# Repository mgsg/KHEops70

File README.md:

# KHEops70 
Keyboard | Hall Effect | OrthoLinear | Programmable | Standard-sized

| WARNING: DIY project. Use at your own risk!

| Forked from the [Moonboard Keyboard](https://github.com/certainly1182/MoonBoard).

<p>&nbsp;&nbsp;&nbsp;&nbsp;&nbsp;&nbsp;&nbsp;&nbsp;</p>

## Features

- 70 HE switches, 60% case, 13x5 + 5 keys + 1 encoder + 2 potentiometers in ortholinear arrangement.
- All keys are 1u. Keycaps in uniform profile preferred (XDA, DSA...).
- QMK Firmware compatibility.
- QMK MIDI Support (Audio support buggy).
- Compatibility with "standard" widely available 60% keyboard cases.
- OLED display.

## Hardware

Design for PCBs can be found in the hardware folder.

<p>&nbsp;&nbsp;&nbsp;&nbsp;&nbsp;&nbsp;&nbsp;&nbsp;</p>

<p>&nbsp;&nbsp;&nbsp;&nbsp;&nbsp;&nbsp;&nbsp;&nbsp;</p>

## Firmware

Compiled firmware provided as is. Largely based on the [Moonboard firmware found here](https://github.com/RephlexZero/qmk_firmware/tree/adc_testing/keyboards/rephlex/moonboard). Modified keyboard.json provided.

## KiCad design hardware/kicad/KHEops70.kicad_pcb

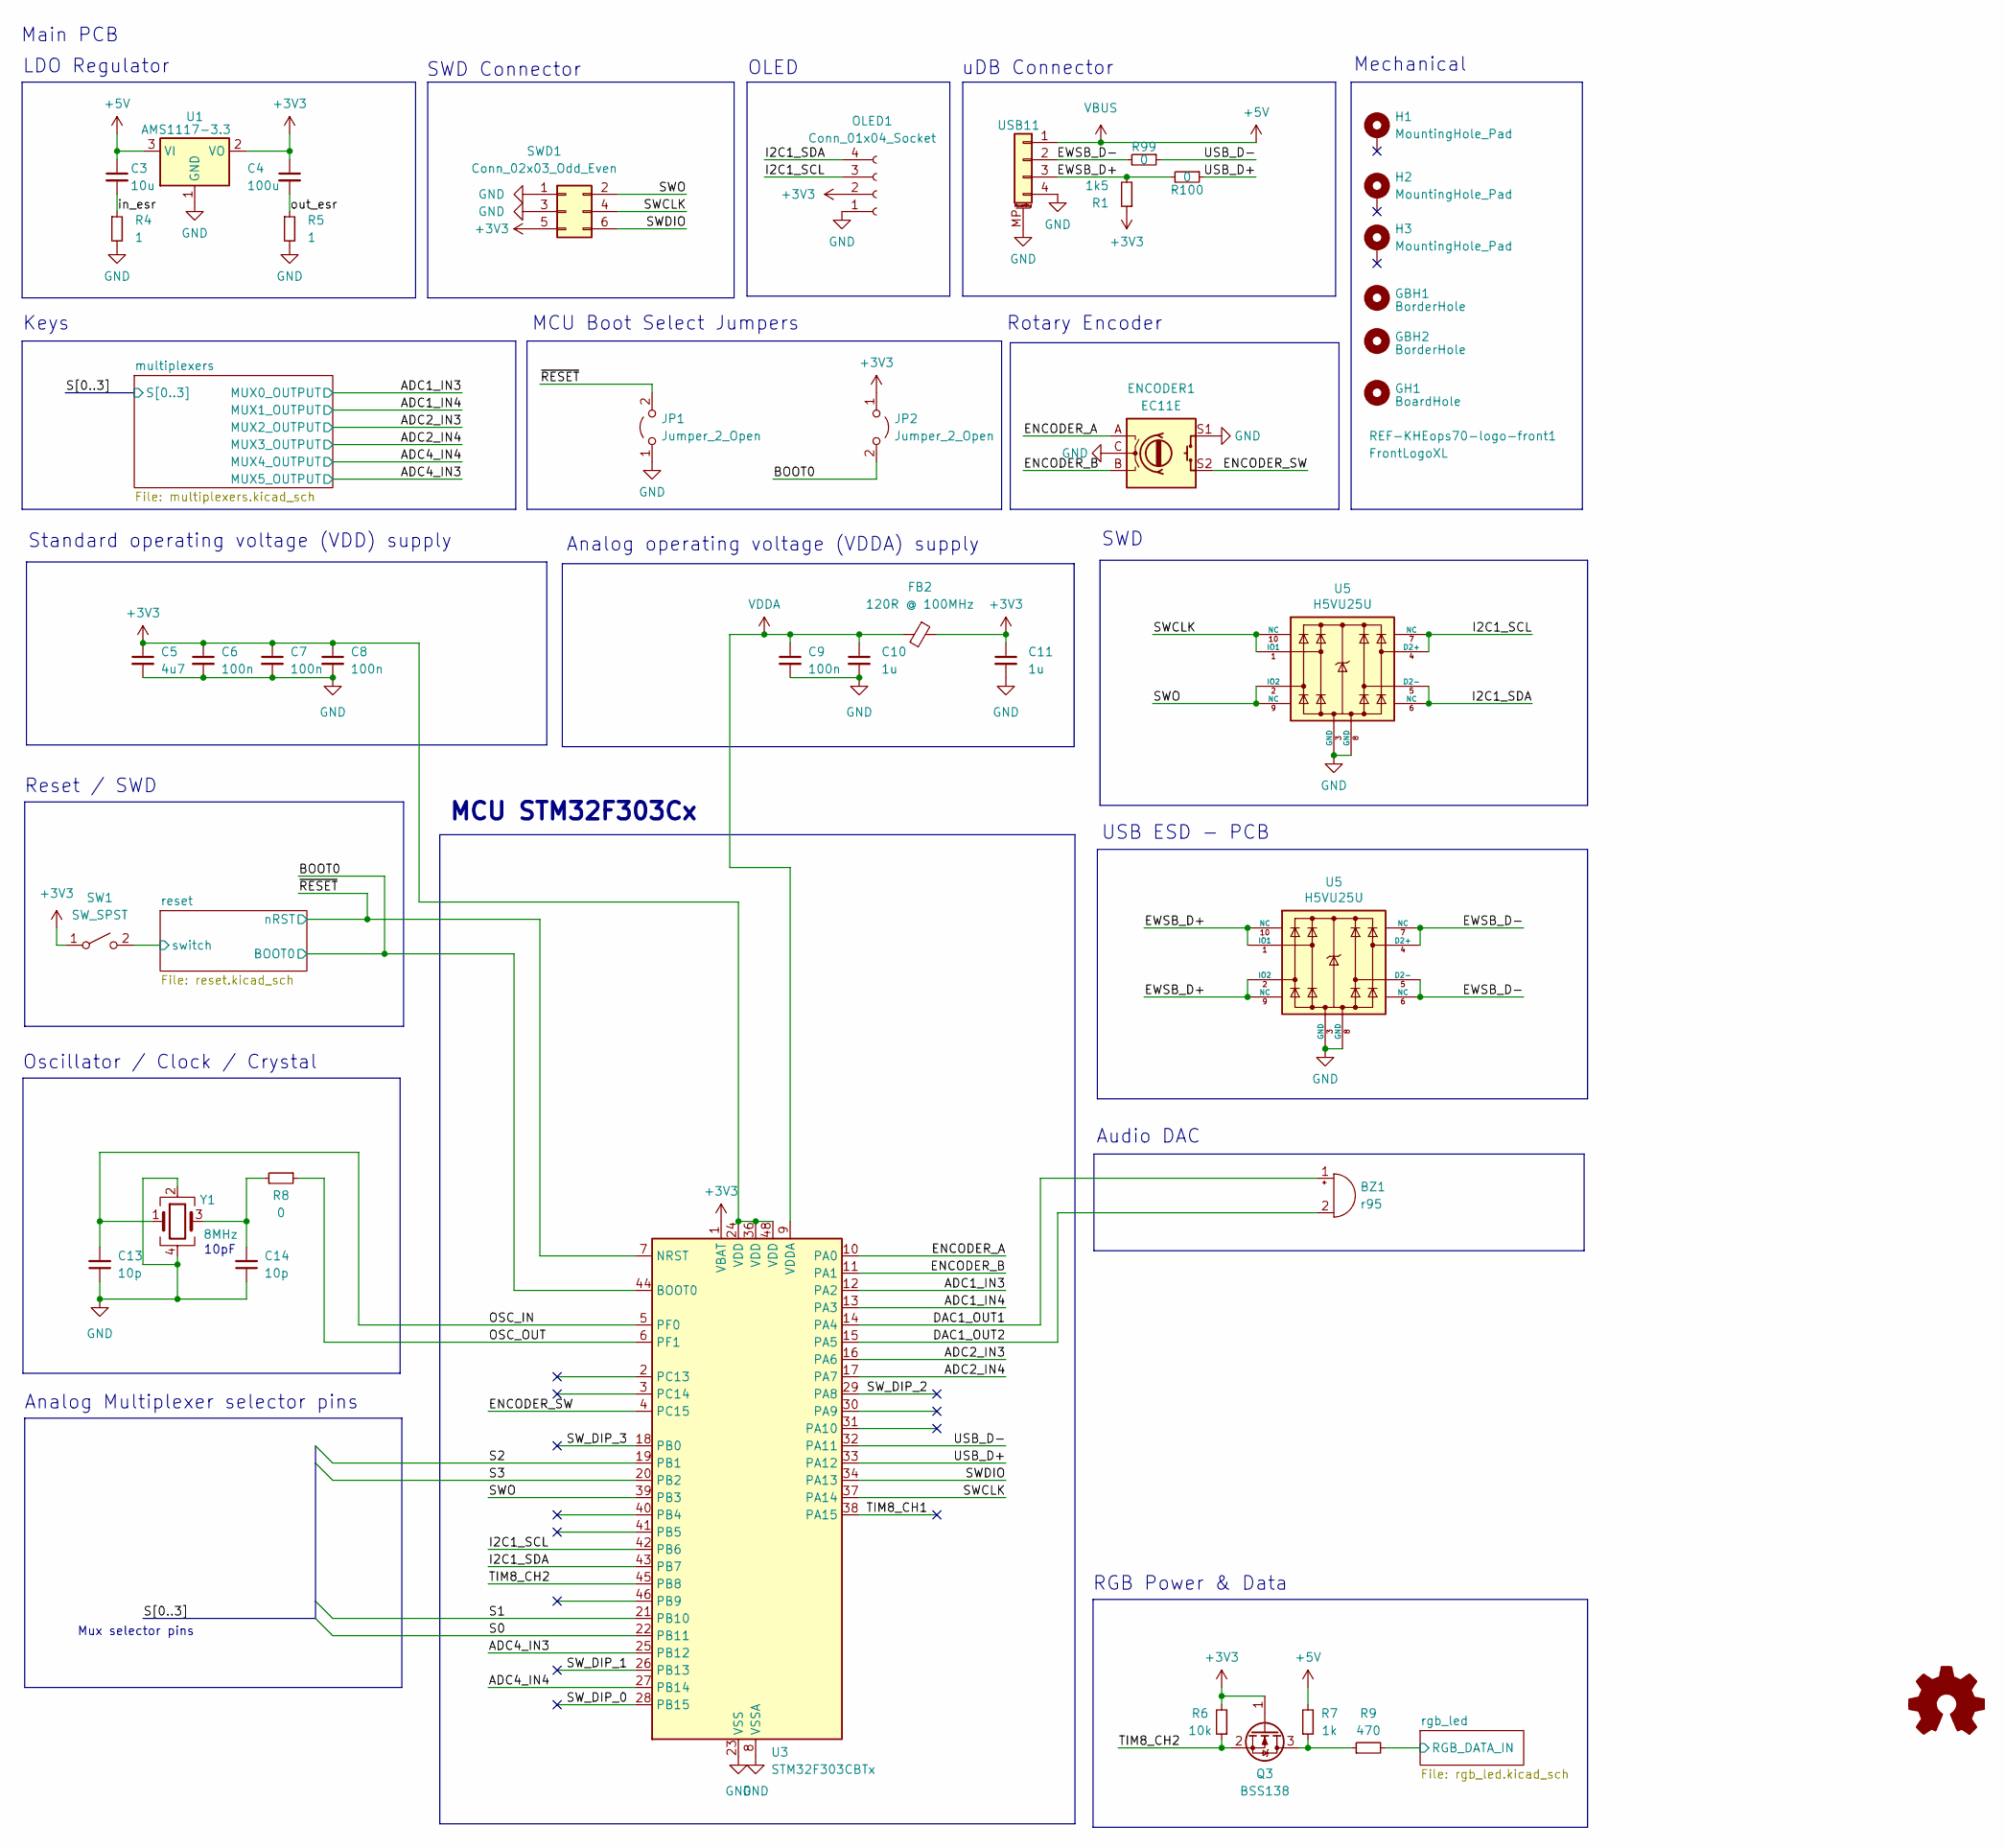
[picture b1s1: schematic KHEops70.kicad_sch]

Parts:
BZ1: r95; Buzzer_Murata_PKLCS1212E; LCSC PN C113159
C3: 10u; C_1206_3216Metric; LCSC C13585
C4: 100u; C_1206_3216Metric; LCSC C15008
C5: 4u7; C_0402_1005Metric; LCSC C23733
C6, C7, C8, C9: 100n; C_0402_1005Metric; LCSC C1525
C10, C11: 1u; C_0402_1005Metric; LCSC C52923
C13, C14: 10p; C_0402_1005Metric; LCSC C32949
ENCODER1: EC11E; ROT_Alps_EC11E-Switch
FB2: 120R @ 100MHz; L_0805_2012Metric; LCSC C79382
GBH1, GBH2: BorderHole; KHEops70-border-hole
GH1: BoardHole; KHEops70-hole
H1, H2, H3: MountingHole_Pad; 2.2mm hole
JP1, JP2: Jumper_2_Open; PinHeader_1x02_P2.54mm_Vertical
LOGO2: (no value)
OLED1: Conn_01x04_Socket; OLED Module
Q3: BSS138; SOT-23; LCSC C5224263
R1: 1k5; R_0805_2012Metric; LCSC C25867
R4, R5: 1; R_1206_3216Metric; LCSC C17928
R6: 10k; R_0805_2012Metric; LCSC C17414
R7: 1k; R_0805_2012Metric; LCSC C17513
R8, R99, R100: 0; R_0603_1608Metric_Pad0.98x0.95mm_HandSolder; LCSC C21189
R9: 470; R_0805_2012Metric; LCSC C25117
REF-KHEops70-logo-front1: FrontLogoXL; KHEops70-logo-xl
SW1: SW_SPST; SW_SPST_TL3342; LCSC C2886897
SWD1: Conn_02x03_Odd_Even; PinHeader_2x03_P2.54mm_Vertical
U1: AMS1117-3.3; SOT-223-3_TabPin2; LCSC C6186
U3: STM32F303CBTx; LQFP-48_7x7mm_P0.5mm; LCSC C108516
U5: H5VU25U; DFN2510; Manufacturer Part Number TPD4E05U06DQAR; LCSC C20615800
USB11: SM04B-SRSS-TB; JST_SH_SM04B-SRSS-TB_1x04-1MP_P1.00mm_Horizontal; Manufacturer Part Number SM04B-SRSS-TB; LCSC C160404
Y1: 8MHz; Crystal_SMD_3225-4Pin_3.2x2.5mm; LCSC C518154

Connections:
+3V3: C4.1, C5.1, C6.1, C7.1, C8.1, C11.1, FB2.1, JP2.1 (A), OLED1.2, Q3.1 (G), R1.1, R6.2, SW1.1 (A), SWD1.5, U1.2 (VO), U3.1 (VBAT), U3.24 (VDD), U3.36 (VDD), U3.48 (VDD); also elsewhere on the board
+5V: C3.1, R7.2, U1.3 (VI), USB11.1; also elsewhere on the board
/ADC1_IN3: U3.12 (PA2); also elsewhere on the board
/ADC2_IN3: U3.16 (PA6); also elsewhere on the board
/ADC2_IN4: U3.17 (PA7); also elsewhere on the board
/ADC4_IN3: U3.25 (PB12); also elsewhere on the board
/ADC4_IN4: U3.27 (PB14); also elsewhere on the board
/BOOT0: JP2.2 (B), U3.44 (BOOT0); also elsewhere on the board
/DAC1_OUT1: BZ1.1 (-), U3.14 (PA4)
/DAC1_OUT2: BZ1.2 (+), U3.15 (PA5)
/ENCODER_A: ENCODER1.A, U3.10 (PA0)
/ENCODER_B: ENCODER1.B, U3.11 (PA1)
/ENCODER_SW: ENCODER1.S2, U3.4 (PC15)
/OSC_IN: C13.2, U3.5 (PF0), Y1.1
/OSC_OUT: R8.1, U3.6 (PF1)
/S1: U3.21 (PB10); also elsewhere on the board
/S2: U3.19 (PB1); also elsewhere on the board
/S3: U3.20 (PB2); also elsewhere on the board
/SWDIO: SWD1.6, U3.34 (PA13)
/SW_DIP_0: U3.28 (PB15)
/SW_DIP_1: U3.26 (PB13)
/SW_DIP_2: U3.29 (PA8)
/SW_DIP_3: U3.18 (PB0)
/TIM8_CH1: U3.38 (PA15)
/TIM8_CH2: Q3.2 (S), R6.1, U3.45 (PB8)
/USB_D+: R100.1, U3.33 (PA12)
/USB_D-: R99.1, U3.32 (PA11)
/in_esr: C3.2, R4.1
/out_esr: C4.2, R5.1
/reset/switch: SW1.2 (B); also elsewhere on the board
/rgb_led/RGB_DATA_IN: R9.2; also elsewhere on the board
/~RESET: JP1.2 (B), U3.7 (NRST); also elsewhere on the board
unnamed: C14.2, R8.2, Y1.3
unnamed: Q3.3 (D), R7.1, R9.1
VDDA: C9.1, C10.1, FB2.2, U3.9 (VDDA)

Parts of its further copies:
U10, U11: H5VU25U; DFN2510; Manufacturer Part Number TPD4E05U06DQAR; LCSC C20615800

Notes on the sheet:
Standard operating voltage (VDD) supply
Mechanical
Keys
Analog Multiplexer selector pins
Mux selector pins
SWD Connector
SWD
OLED
Audio DAC
10pF
MCU Boot Select Jumpers
USB ESD - PCB
RGB Power & Data
Reset / SWD
Rotary Encoder
Analog operating voltage (VDDA) supply
uDB Connector
MCU STM32F303Cx
LDO Regulator
Main PCB
Oscillator / Clock / Crystal

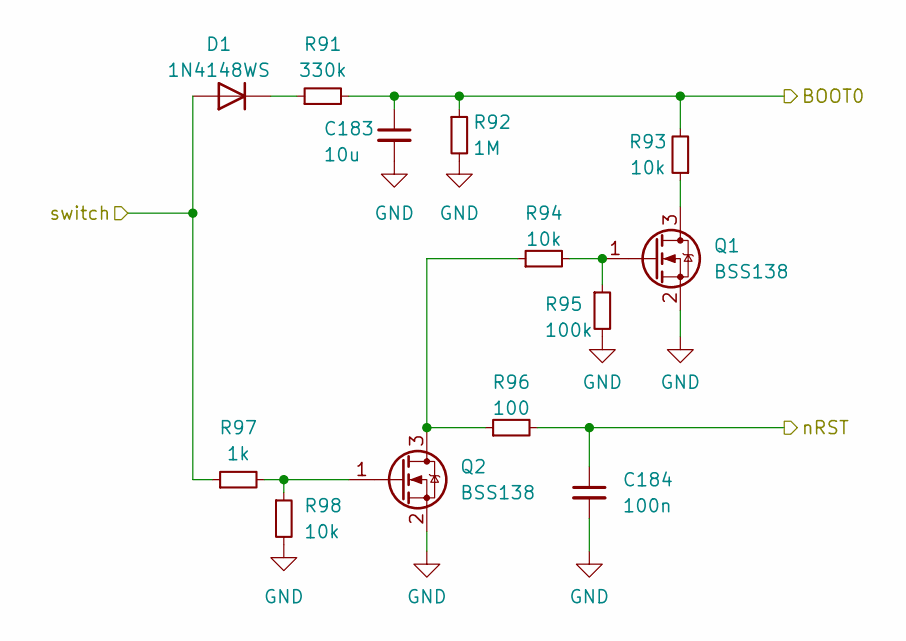
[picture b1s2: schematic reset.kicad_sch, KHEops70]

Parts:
C183: 10u; C_1206_3216Metric; LCSC C13585
C184: 100n; C_0805_2012Metric; LCSC C49678
D1: 1N4148WS; D_SOD-323; LCSC C2128
Q1, Q2: BSS138; SOT-23; LCSC C5224263
R91: 330k; R_0603_1608Metric; LCSC C23137
R92: 1M; R_0603_1608Metric; LCSC C22935
R93, R98: 10k; R_0603_1608Metric; LCSC C17414
R94: 10k; R_0805_2012Metric; LCSC C17414
R95: 100k; R_0805_2012Metric; LCSC C25741
R96: 100; R_0805_2012Metric; LCSC C25076
R97: 1k; R_0603_1608Metric; LCSC C21190

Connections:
/BOOT0: C183.1, R91.2, R92.1, R93.2; also elsewhere on the board
/reset/switch: D1.2 (A), R97.1; also elsewhere on the board
/~RESET: C184.1, R96.2; also elsewhere on the board
unnamed: D1.1 (K), R91.1
unnamed: Q1.3 (D), R93.1
unnamed: Q1.1 (G), R94.2, R95.1
unnamed: Q2.3 (D), R94.1, R96.1
unnamed: Q2.1 (G), R97.2, R98.1

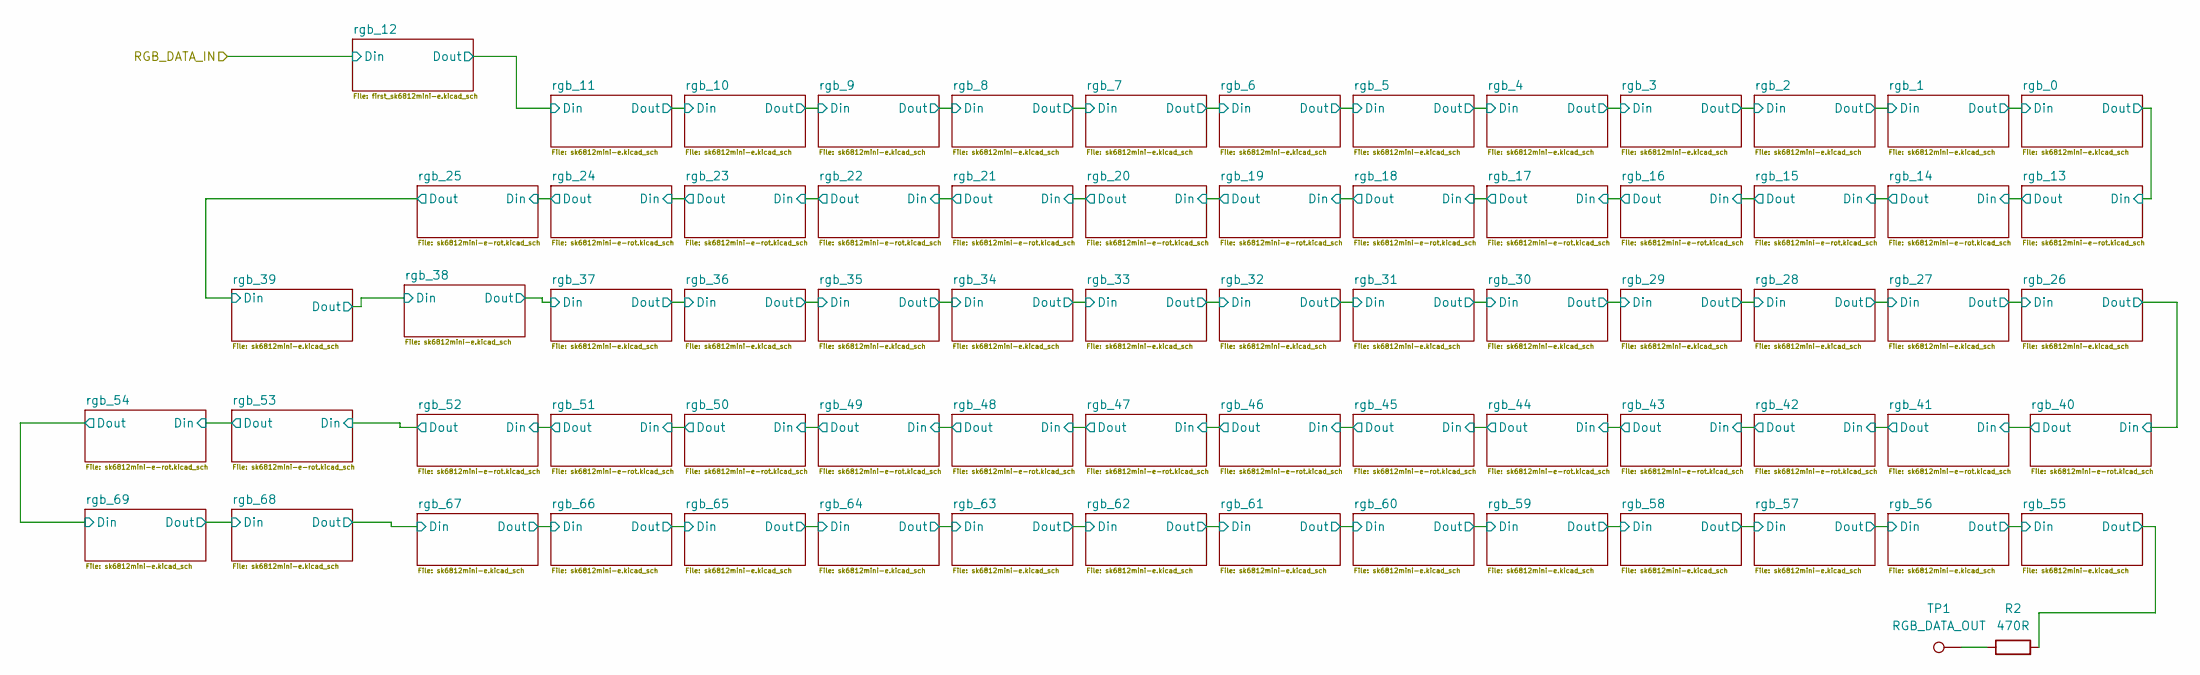
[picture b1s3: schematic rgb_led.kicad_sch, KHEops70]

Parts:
R2: 470R; R_0805_2012Metric; LCSC C25117
TP1: RGB_DATA_OUT; TestPoint_Pad_D1.5mm

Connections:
/rgb_led/rgb_55/Dout: R2.2; also elsewhere on the board
unnamed: R2.1, TP1.1

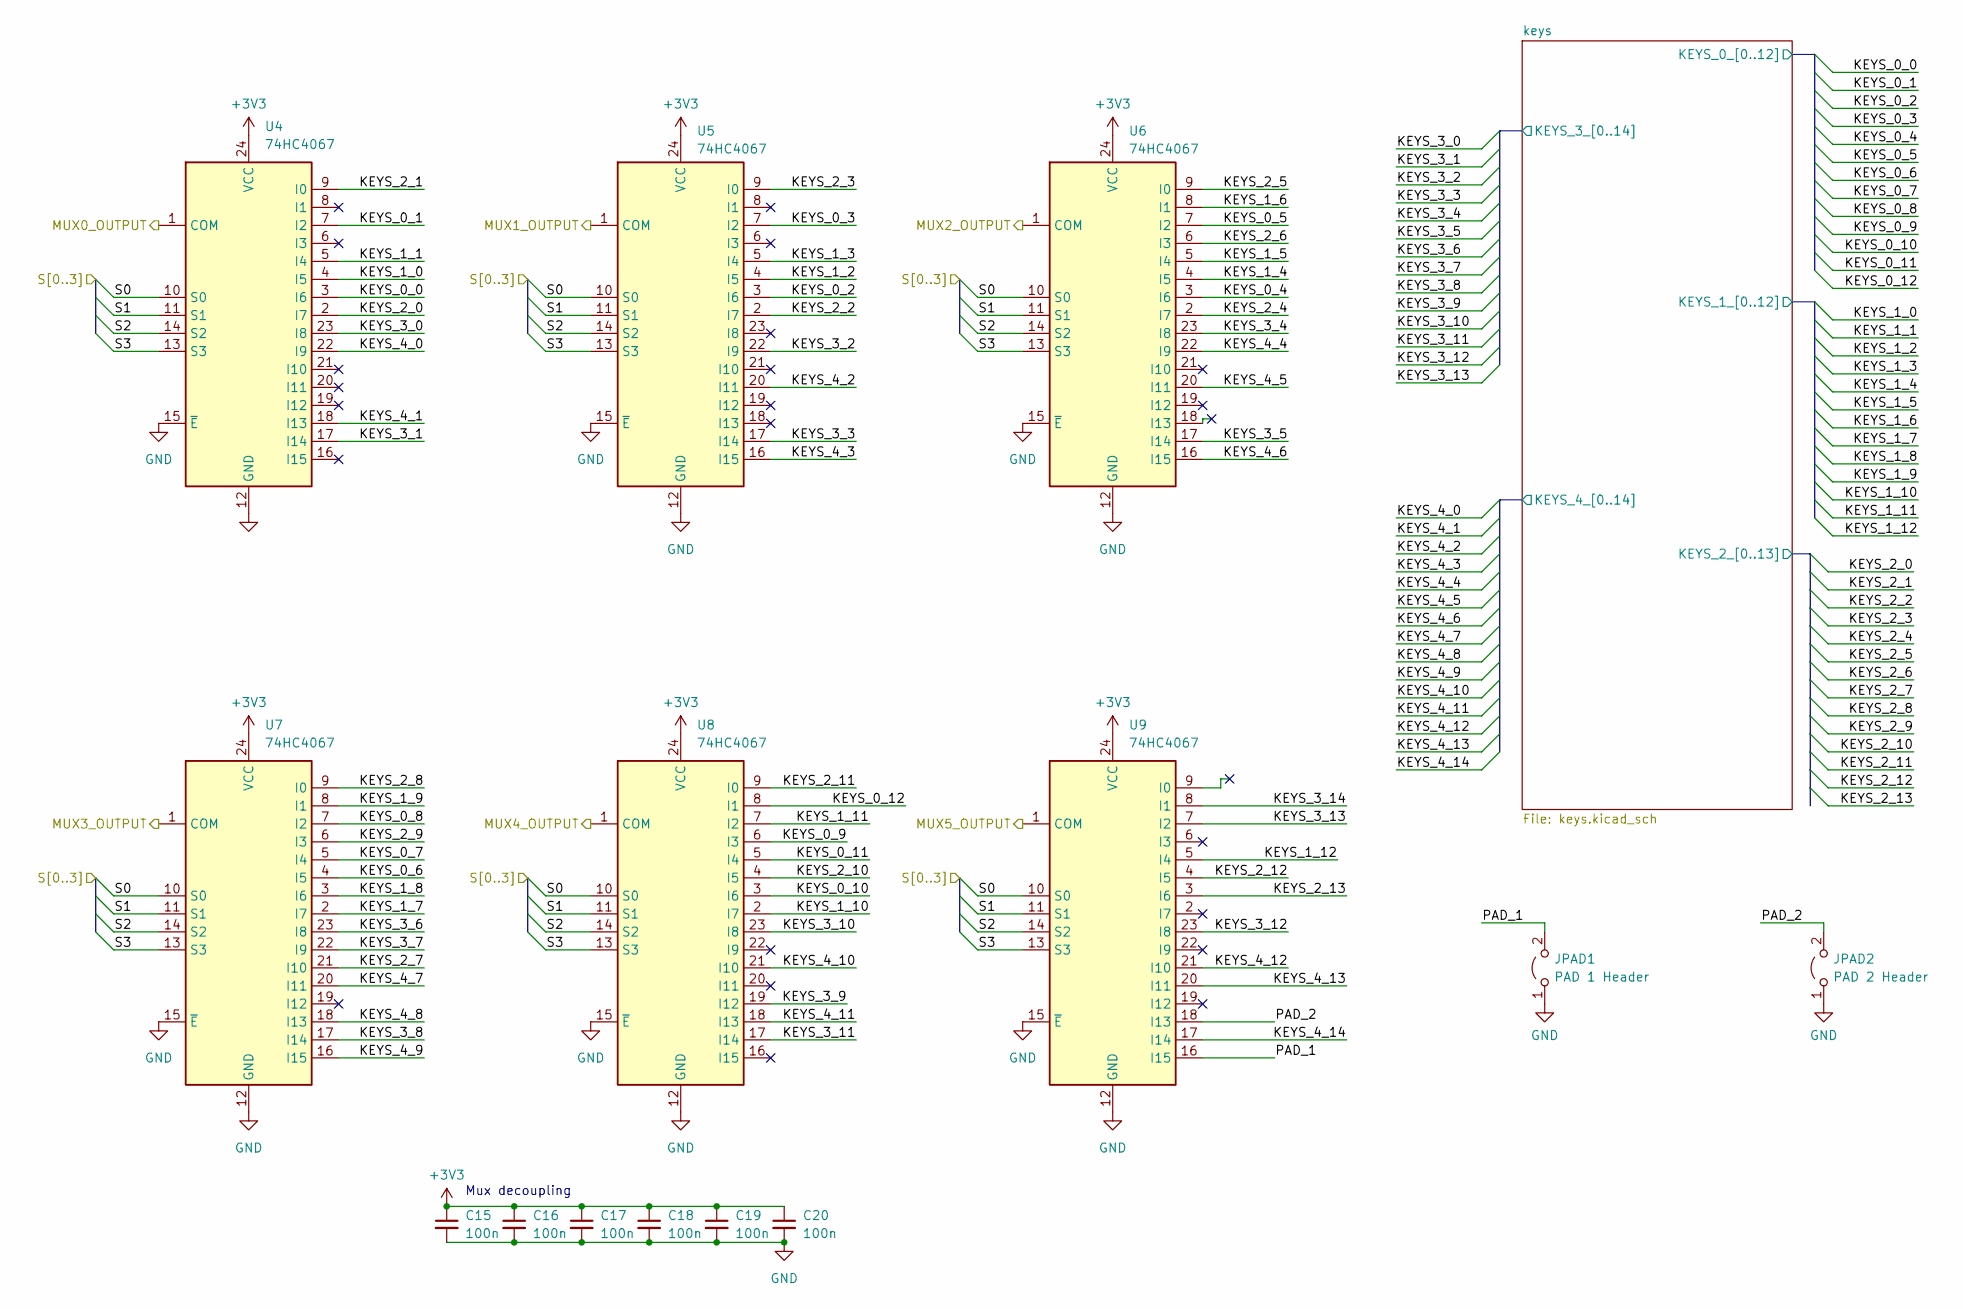
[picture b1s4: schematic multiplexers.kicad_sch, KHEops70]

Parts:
C15, C16, C17, C18, C19, C20: 100n; C_0805_2012Metric; LCSC C49678
JPAD1: PAD 1 Header; PinHeader_1x02_P2.54mm_Vertical
JPAD2: PAD 2 Header; PinHeader_1x02_P2.54mm_Vertical
U4, U5, U6, U7, U8, U9: 74HC4067; TSSOP-24_4.4x7.8mm_P0.65mm; LCSC C179326

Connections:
+3V3: C15.1, C16.1, C17.1, C18.1, C19.1, C20.1, U4.24 (VCC), U5.24 (VCC), U6.24 (VCC), U7.24 (VCC), U8.24 (VCC), U9.24 (VCC); also elsewhere on the board
/ADC1_IN3: U4.1 (COM); also elsewhere on the board
/ADC2_IN3: U6.1 (COM); also elsewhere on the board
/ADC2_IN4: U7.1 (COM); also elsewhere on the board
/ADC4_IN3: U9.1 (COM); also elsewhere on the board
/ADC4_IN4: U8.1 (COM); also elsewhere on the board
/S1: U4.11 (S1), U5.11 (S1), U6.11 (S1), U7.11 (S1), U8.11 (S1), U9.11 (S1); also elsewhere on the board
/S2: U4.14 (S2), U5.14 (S2), U6.14 (S2), U7.14 (S2), U8.14 (S2), U9.14 (S2); also elsewhere on the board
/S3: U4.13 (S3), U5.13 (S3), U6.13 (S3), U7.13 (S3), U8.13 (S3), U9.13 (S3); also elsewhere on the board
/multiplexers/PAD_1: JPAD1.2 (B), U9.16 (I15)
/multiplexers/PAD_2: JPAD2.2 (B), U9.18 (I13)
/multiplexers/keys/KEYS_0_0: U4.3 (I6); also elsewhere on the board
/multiplexers/keys/KEYS_0_1: U4.7 (I2); also elsewhere on the board
/multiplexers/keys/KEYS_0_4: U6.3 (I6); also elsewhere on the board
/multiplexers/keys/KEYS_0_5: U6.7 (I2); also elsewhere on the board
/multiplexers/keys/KEYS_0_6: U7.4 (I5); also elsewhere on the board
/multiplexers/keys/KEYS_0_7: U7.5 (I4); also elsewhere on the board
/multiplexers/keys/KEYS_0_8: U7.7 (I2); also elsewhere on the board
/multiplexers/keys/KEYS_0_9: U8.6 (I3); also elsewhere on the board
/multiplexers/keys/KEYS_0_10: U8.3 (I6); also elsewhere on the board
/multiplexers/keys/KEYS_0_11: U8.5 (I4); also elsewhere on the board
/multiplexers/keys/KEYS_0_12: U8.8 (I1); also elsewhere on the board
/multiplexers/keys/KEYS_1_0: U4.4 (I5); also elsewhere on the board
/multiplexers/keys/KEYS_1_1: U4.5 (I4); also elsewhere on the board
/multiplexers/keys/KEYS_1_4: U6.4 (I5); also elsewhere on the board
/multiplexers/keys/KEYS_1_5: U6.5 (I4); also elsewhere on the board
/multiplexers/keys/KEYS_1_6: U6.8 (I1); also elsewhere on the board
/multiplexers/keys/KEYS_1_7: U7.2 (I7); also elsewhere on the board
/multiplexers/keys/KEYS_1_8: U7.3 (I6); also elsewhere on the board
/multiplexers/keys/KEYS_1_9: U7.8 (I1); also elsewhere on the board
/multiplexers/keys/KEYS_1_10: U8.2 (I7); also elsewhere on the board
/multiplexers/keys/KEYS_1_11: U8.7 (I2); also elsewhere on the board
/multiplexers/keys/KEYS_1_12: U9.5 (I4); also elsewhere on the board
/multiplexers/keys/KEYS_2_0: U4.2 (I7); also elsewhere on the board
/multiplexers/keys/KEYS_2_1: U4.9 (I0); also elsewhere on the board
/multiplexers/keys/KEYS_2_4: U6.2 (I7); also elsewhere on the board
/multiplexers/keys/KEYS_2_5: U6.9 (I0); also elsewhere on the board
/multiplexers/keys/KEYS_2_6: U6.6 (I3); also elsewhere on the board
/multiplexers/keys/KEYS_2_7: U7.21 (I10); also elsewhere on the board
/multiplexers/keys/KEYS_2_8: U7.9 (I0); also elsewhere on the board
/multiplexers/keys/KEYS_2_9: U7.6 (I3); also elsewhere on the board
/multiplexers/keys/KEYS_2_10: U8.4 (I5); also elsewhere on the board
/multiplexers/keys/KEYS_2_11: U8.9 (I0); also elsewhere on the board
/multiplexers/keys/KEYS_2_12: U9.4 (I5); also elsewhere on the board
/multiplexers/keys/KEYS_2_13: U9.3 (I6); also elsewhere on the board
/multiplexers/keys/KEYS_3_0: U4.23 (I8); also elsewhere on the board
/multiplexers/keys/KEYS_3_1: U4.17 (I14); also elsewhere on the board
/multiplexers/keys/KEYS_3_2: U5.22 (I9); also elsewhere on the board
/multiplexers/keys/KEYS_3_3: U5.17 (I14); also elsewhere on the board
/multiplexers/keys/KEYS_3_4: U6.23 (I8); also elsewhere on the board
/multiplexers/keys/KEYS_3_5: U6.17 (I14); also elsewhere on the board
/multiplexers/keys/KEYS_3_6: U7.23 (I8); also elsewhere on the board
/multiplexers/keys/KEYS_3_7: U7.22 (I9); also elsewhere on the board
/multiplexers/keys/KEYS_3_8: U7.17 (I14); also elsewhere on the board
/multiplexers/keys/KEYS_3_9: U8.19 (I12); also elsewhere on the board
/multiplexers/keys/KEYS_3_10: U8.23 (I8); also elsewhere on the board
/multiplexers/keys/KEYS_3_11: U8.17 (I14); also elsewhere on the board
/multiplexers/keys/KEYS_3_12: U9.23 (I8); also elsewhere on the board
/multiplexers/keys/KEYS_3_13: U9.7 (I2); also elsewhere on the board
/multiplexers/keys/KEYS_3_14: U9.8 (I1); also elsewhere on the board
/multiplexers/keys/KEYS_4_0: U4.22 (I9); also elsewhere on the board
/multiplexers/keys/KEYS_4_1: U4.18 (I13); also elsewhere on the board
/multiplexers/keys/KEYS_4_2: U5.20 (I11); also elsewhere on the board
/multiplexers/keys/KEYS_4_3: U5.16 (I15); also elsewhere on the board
/multiplexers/keys/KEYS_4_4: U6.22 (I9); also elsewhere on the board
/multiplexers/keys/KEYS_4_5: U6.20 (I11); also elsewhere on the board
/multiplexers/keys/KEYS_4_6: U6.16 (I15); also elsewhere on the board
/multiplexers/keys/KEYS_4_7: U7.20 (I11); also elsewhere on the board
/multiplexers/keys/KEYS_4_8: U7.18 (I13); also elsewhere on the board
/multiplexers/keys/KEYS_4_9: U7.16 (I15); also elsewhere on the board
/multiplexers/keys/KEYS_4_10: U8.21 (I10); also elsewhere on the board
/multiplexers/keys/KEYS_4_11: U8.18 (I13); also elsewhere on the board
/multiplexers/keys/KEYS_4_12: U9.21 (I10); also elsewhere on the board
/multiplexers/keys/KEYS_4_13: U9.20 (I11); also elsewhere on the board
/multiplexers/keys/KEYS_4_14: U9.17 (I14); also elsewhere on the board

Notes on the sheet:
Mux decoupling

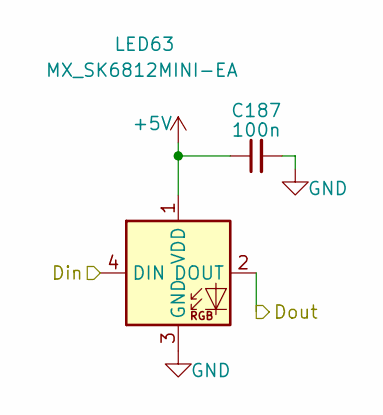
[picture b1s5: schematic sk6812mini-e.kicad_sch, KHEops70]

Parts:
C187: 100n; C_0805_2012Metric; LCSC C49678
LED63: MX_SK6812MINI-EA; SK 6812 MINI-EA; LCSC C5378731

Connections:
+5V: C187.1, LED63.1 (VDD); also elsewhere on the board
/rgb_led/rgb_62/Din: LED63.2 (DOUT); also elsewhere on the board
/rgb_led/rgb_63/Din: LED63.4 (DIN); also elsewhere on the board

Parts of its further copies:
C74, C101, C102, C103, C104, C131, C132, C163, C164, C165, C166, C167, C168, C169, C170, C171, C172, C173, C174, C175, C176, C177, C178, C179, C180, C181, C182, C185, C186, C188, C189, C190, C191, C192, C193, C194, C195, C268, C271, C274: 100n; C_0805_2012Metric; LCSC C49678
LED0, LED1, LED2, LED3, LED4, LED5, LED6, LED7, LED8, LED9, LED10, LED11, LED26, LED27, LED28, LED29, LED30, LED31, LED32, LED33, LED34, LED35, LED36, LED37, LED38, LED39, LED55, LED56, LED57, LED58, LED59, LED60, LED61, LED62, LED64, LED65, LED66, LED67, LED68, LED69: MX_SK6812MINI-EA; SK 6812 MINI-EA; LCSC C5378731

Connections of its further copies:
+5V: C74.1, C101.1, C102.1, C103.1, C104.1, C131.1, C132.1, C163.1, C164.1, C165.1, C166.1, C167.1, C168.1, C169.1, C170.1, C171.1, C172.1, C173.1, C174.1, C175.1, C176.1, C177.1, C178.1, C179.1, C180.1, C181.1, C182.1, C185.1, C186.1, C188.1, C189.1, C190.1, C191.1, C192.1, C193.1, C194.1, C195.1, C268.1, C271.1, C274.1, LED0.1 (VDD), LED1.1 (VDD), LED2.1 (VDD), LED3.1 (VDD), LED4.1 (VDD), LED5.1 (VDD), LED6.1 (VDD), LED7.1 (VDD), LED8.1 (VDD), LED9.1 (VDD), LED10.1 (VDD), LED11.1 (VDD), LED26.1 (VDD), LED27.1 (VDD), LED28.1 (VDD), LED29.1 (VDD), LED30.1 (VDD), LED31.1 (VDD), LED32.1 (VDD), LED33.1 (VDD), LED34.1 (VDD), LED35.1 (VDD), LED36.1 (VDD), LED37.1 (VDD), LED38.1 (VDD), LED39.1 (VDD), LED55.1 (VDD), LED56.1 (VDD), LED57.1 (VDD), LED58.1 (VDD), LED59.1 (VDD), LED60.1 (VDD), LED61.1 (VDD), LED62.1 (VDD), LED64.1 (VDD), LED65.1 (VDD), LED66.1 (VDD), LED67.1 (VDD), LED68.1 (VDD), LED69.1 (VDD); also elsewhere on the board
/rgb_led/rgb_0/Din: LED0.4 (DIN), LED1.2 (DOUT)
/rgb_led/rgb_0/Dout: LED0.2 (DOUT); also elsewhere on the board
/rgb_led/rgb_1/Din: LED1.4 (DIN), LED2.2 (DOUT)
/rgb_led/rgb_2/Din: LED2.4 (DIN), LED3.2 (DOUT)
/rgb_led/rgb_3/Din: LED3.4 (DIN), LED4.2 (DOUT)
/rgb_led/rgb_4/Din: LED4.4 (DIN), LED5.2 (DOUT)
/rgb_led/rgb_5/Din: LED5.4 (DIN), LED6.2 (DOUT)
/rgb_led/rgb_6/Din: LED6.4 (DIN), LED7.2 (DOUT)
/rgb_led/rgb_7/Din: LED7.4 (DIN), LED8.2 (DOUT)
/rgb_led/rgb_8/Din: LED8.4 (DIN), LED9.2 (DOUT)
/rgb_led/rgb_10/Din: LED10.4 (DIN), LED11.2 (DOUT)
/rgb_led/rgb_10/Dout: LED9.4 (DIN), LED10.2 (DOUT)
/rgb_led/rgb_11/Din: LED11.4 (DIN); also elsewhere on the board
/rgb_led/rgb_25/Dout: LED39.4 (DIN); also elsewhere on the board
/rgb_led/rgb_26/Din: LED26.4 (DIN), LED27.2 (DOUT)
/rgb_led/rgb_26/Dout: LED26.2 (DOUT); also elsewhere on the board
/rgb_led/rgb_27/Din: LED27.4 (DIN), LED28.2 (DOUT)
/rgb_led/rgb_28/Din: LED28.4 (DIN), LED29.2 (DOUT)
/rgb_led/rgb_29/Din: LED29.4 (DIN), LED30.2 (DOUT)
/rgb_led/rgb_30/Din: LED30.4 (DIN), LED31.2 (DOUT)
/rgb_led/rgb_31/Din: LED31.4 (DIN), LED32.2 (DOUT)
/rgb_led/rgb_32/Din: LED32.4 (DIN), LED33.2 (DOUT)
/rgb_led/rgb_33/Din: LED33.4 (DIN), LED34.2 (DOUT)
/rgb_led/rgb_34/Din: LED34.4 (DIN), LED35.2 (DOUT)
/rgb_led/rgb_35/Din: LED35.4 (DIN), LED36.2 (DOUT)
/rgb_led/rgb_36/Din: LED36.4 (DIN), LED37.2 (DOUT)
/rgb_led/rgb_37/Din: LED37.4 (DIN), LED38.2 (DOUT)
/rgb_led/rgb_38/Din: LED38.4 (DIN), LED39.2 (DOUT)
/rgb_led/rgb_54/Dout: LED69.4 (DIN); also elsewhere on the board
/rgb_led/rgb_55/Din: LED55.4 (DIN), LED56.2 (DOUT)
/rgb_led/rgb_55/Dout: LED55.2 (DOUT); also elsewhere on the board
/rgb_led/rgb_56/Din: LED56.4 (DIN), LED57.2 (DOUT)
/rgb_led/rgb_57/Din: LED57.4 (DIN), LED58.2 (DOUT)
/rgb_led/rgb_58/Din: LED58.4 (DIN), LED59.2 (DOUT)
/rgb_led/rgb_59/Din: LED59.4 (DIN), LED60.2 (DOUT)
/rgb_led/rgb_60/Din: LED60.4 (DIN), LED61.2 (DOUT)
/rgb_led/rgb_61/Din: LED61.4 (DIN), LED62.2 (DOUT)
/rgb_led/rgb_62/Din: LED62.4 (DIN); also elsewhere on the board
/rgb_led/rgb_63/Din: LED64.2 (DOUT); also elsewhere on the board
/rgb_led/rgb_64/Din: LED64.4 (DIN), LED65.2 (DOUT)
/rgb_led/rgb_65/Din: LED65.4 (DIN), LED66.2 (DOUT)
/rgb_led/rgb_66/Din: LED66.4 (DIN), LED67.2 (DOUT)
/rgb_led/rgb_67/Din: LED67.4 (DIN), LED68.2 (DOUT)
/rgb_led/rgb_68/Din: LED68.4 (DIN), LED69.2 (DOUT)

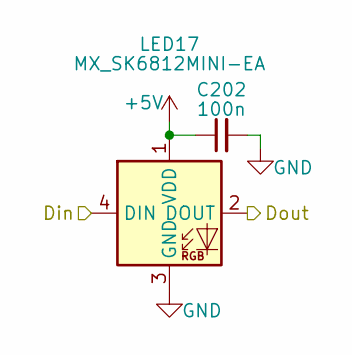
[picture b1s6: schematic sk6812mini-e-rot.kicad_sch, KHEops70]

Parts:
C202: 100n; C_0805_2012Metric; LCSC C49678
LED17: MX_SK6812MINI-EA; SK 6812 MINI-EA-ROT; LCSC C5378731

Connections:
+5V: C202.1, LED17.1 (VDD); also elsewhere on the board
/rgb_led/rgb_16/Dout: LED17.4 (DIN); also elsewhere on the board
/rgb_led/rgb_17/Dout: LED17.2 (DOUT); also elsewhere on the board

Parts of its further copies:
C198, C199, C200, C201, C203, C204, C205, C206, C207, C208, C209, C210, C225, C226, C227, C228, C229, C230, C231, C232, C233, C234, C235, C236, C237, C262, C265: 100n; C_0805_2012Metric; LCSC C49678
LED13, LED14, LED15, LED16, LED18, LED19, LED20, LED21, LED22, LED23, LED24, LED25, LED40, LED41, LED42, LED43, LED44, LED45, LED46, LED47, LED48, LED49, LED50, LED51, LED52, LED53, LED54: MX_SK6812MINI-EA; SK 6812 MINI-EA-ROT; LCSC C5378731

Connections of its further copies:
+5V: C198.1, C199.1, C200.1, C201.1, C203.1, C204.1, C205.1, C206.1, C207.1, C208.1, C209.1, C210.1, C225.1, C226.1, C227.1, C228.1, C229.1, C230.1, C231.1, C232.1, C233.1, C234.1, C235.1, C236.1, C237.1, C262.1, C265.1, LED13.1 (VDD), LED14.1 (VDD), LED15.1 (VDD), LED16.1 (VDD), LED18.1 (VDD), LED19.1 (VDD), LED20.1 (VDD), LED21.1 (VDD), LED22.1 (VDD), LED23.1 (VDD), LED24.1 (VDD), LED25.1 (VDD), LED40.1 (VDD), LED41.1 (VDD), LED42.1 (VDD), LED43.1 (VDD), LED44.1 (VDD), LED45.1 (VDD), LED46.1 (VDD), LED47.1 (VDD), LED48.1 (VDD), LED49.1 (VDD), LED50.1 (VDD), LED51.1 (VDD), LED52.1 (VDD), LED53.1 (VDD), LED54.1 (VDD); also elsewhere on the board
/rgb_led/rgb_0/Dout: LED13.4 (DIN); also elsewhere on the board
/rgb_led/rgb_13/Dout: LED13.2 (DOUT), LED14.4 (DIN)
/rgb_led/rgb_14/Dout: LED14.2 (DOUT), LED15.4 (DIN)
/rgb_led/rgb_15/Dout: LED15.2 (DOUT), LED16.4 (DIN)
/rgb_led/rgb_16/Dout: LED16.2 (DOUT); also elsewhere on the board
/rgb_led/rgb_17/Dout: LED18.4 (DIN); also elsewhere on the board
/rgb_led/rgb_18/Dout: LED18.2 (DOUT), LED19.4 (DIN)
/rgb_led/rgb_19/Dout: LED19.2 (DOUT), LED20.4 (DIN)
/rgb_led/rgb_20/Dout: LED20.2 (DOUT), LED21.4 (DIN)
/rgb_led/rgb_21/Dout: LED21.2 (DOUT), LED22.4 (DIN)
/rgb_led/rgb_22/Dout: LED22.2 (DOUT), LED23.4 (DIN)
/rgb_led/rgb_23/Dout: LED23.2 (DOUT), LED24.4 (DIN)
/rgb_led/rgb_24/Dout: LED24.2 (DOUT), LED25.4 (DIN)
/rgb_led/rgb_25/Dout: LED25.2 (DOUT); also elsewhere on the board
/rgb_led/rgb_26/Dout: LED40.4 (DIN); also elsewhere on the board
/rgb_led/rgb_40/Dout: LED40.2 (DOUT), LED41.4 (DIN)
/rgb_led/rgb_41/Dout: LED41.2 (DOUT), LED42.4 (DIN)
/rgb_led/rgb_42/Dout: LED42.2 (DOUT), LED43.4 (DIN)
/rgb_led/rgb_43/Dout: LED43.2 (DOUT), LED44.4 (DIN)
/rgb_led/rgb_44/Dout: LED44.2 (DOUT), LED45.4 (DIN)
/rgb_led/rgb_45/Dout: LED45.2 (DOUT), LED46.4 (DIN)
/rgb_led/rgb_46/Dout: LED46.2 (DOUT), LED47.4 (DIN)
/rgb_led/rgb_47/Dout: LED47.2 (DOUT), LED48.4 (DIN)
/rgb_led/rgb_48/Dout: LED48.2 (DOUT), LED49.4 (DIN)
/rgb_led/rgb_49/Dout: LED49.2 (DOUT), LED50.4 (DIN)
/rgb_led/rgb_50/Dout: LED50.2 (DOUT), LED51.4 (DIN)
/rgb_led/rgb_51/Dout: LED51.2 (DOUT), LED52.4 (DIN)
/rgb_led/rgb_52/Dout: LED52.2 (DOUT), LED53.4 (DIN)
/rgb_led/rgb_53/Dout: LED53.2 (DOUT), LED54.4 (DIN)
/rgb_led/rgb_54/Dout: LED54.2 (DOUT); also elsewhere on the board

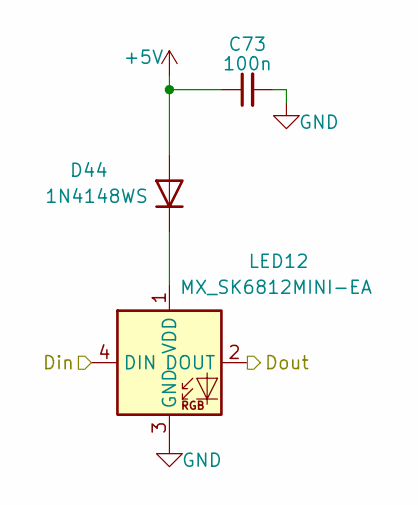
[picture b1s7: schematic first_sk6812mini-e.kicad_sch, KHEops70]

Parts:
C73: 100n; C_0805_2012Metric; LCSC C49678
D44: 1N4148WS; D_SOD-323; LCSC C2128
LED12: MX_SK6812MINI-EA; SK 6812 MINI-EA; LCSC C5378731

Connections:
+5V: C73.1, D44.2 (A); also elsewhere on the board
/rgb_led/RGB_DATA_IN: LED12.4 (DIN); also elsewhere on the board
/rgb_led/rgb_11/Din: LED12.2 (DOUT); also elsewhere on the board
unnamed: D44.1 (K), LED12.1 (VDD)
